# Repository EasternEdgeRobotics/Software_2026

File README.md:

# Software_2026

[Eastern Edge Robotics](https://www.easternedgerobotics.com/) (EER) is a student-led engineering design team based at the Memorial University of Newfoundland and the Fisheries and Marine Institute. The team competes in the annual MATE ROV Competition. Every year at EER, we build a small remotely-operated vehicle (ROV). This repository is EER's 2026 software package.

This code repository contains code for maintaining EER's current ROV, BlueStar.

## Table of Contents

- [Repository Structure](#repository-structure) 
    - [ros_workspace](#ros_workspace) 
    - [Tools](#Tools) 
    - [Assets](#Assets) 
    - [science_officer](#science_officer)

## Repository Structure

### ros_workspace
This project uses ROS2 Jazzy.

#### ROS2 Packages
| Package Name                                                            | Description                                                                                |
|-------------------------------------------------------------------------|--------------------------------------------------------------------------------------------|
| [**bluestar_backend**](./ros_workspace/src/bluestar_backend/)           | Backend code for interfacing with the ROV named BlueStar.                                  |
| [**bluestar_frotnend**](./ros_workspace/src/bluestar_frontend/)         | A C++ GUI for BlueStar made with ImGui, meant for driving the ROV named BlueStar.          |
| [**common_backend**](./ros_workspace/src/common_backend/)               | Common backend ROS nodes for all ROVs.                                                     |
| [**eer_interfaces**](./ros_workspace/src/eer_interfaces/)               | Custom ROS2 interfaces used by all packages.                                               |

More details [here](./ros_workspace/)

### Tools
Assorted tools useful for BlueStar, or developing for BlueStar.

### Assets
Assets used in BlueStar.

### science_officer
Tools related to the science officer tasks in the MATE 2026 mission.

### Firmware
The firmware running on BlueStar's onboard RP2040 microcontroller, which communicates with the onboard Raspberry Pi 4B via I2c, along with the PCB schematics can be found in the [Electrical_2026 Repository](https://github.com/EasternEdgeRobotics/Electrical_2026).

### Agentic AI Tools
Agentic AI tools, such as the Github Copilot Extension, should automatically use the [copilot-instructions.md](./.github/copilot-instructions.md) file for context. This file contains useful technical information for onboarding in natural language.

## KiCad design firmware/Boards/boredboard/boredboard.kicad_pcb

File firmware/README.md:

# Firmware

## LapisLazuli

The [LapisLazuli](./LapisLazuli/) folder contains the firmware for the RP2040 onboard Bluestar's tooling board (called LapisLazuli). It includes code for interfacing with the topides code (see [ros_workpace](../ros_workspace/README.md)) via UART and controlling Bluestar's peripherals.

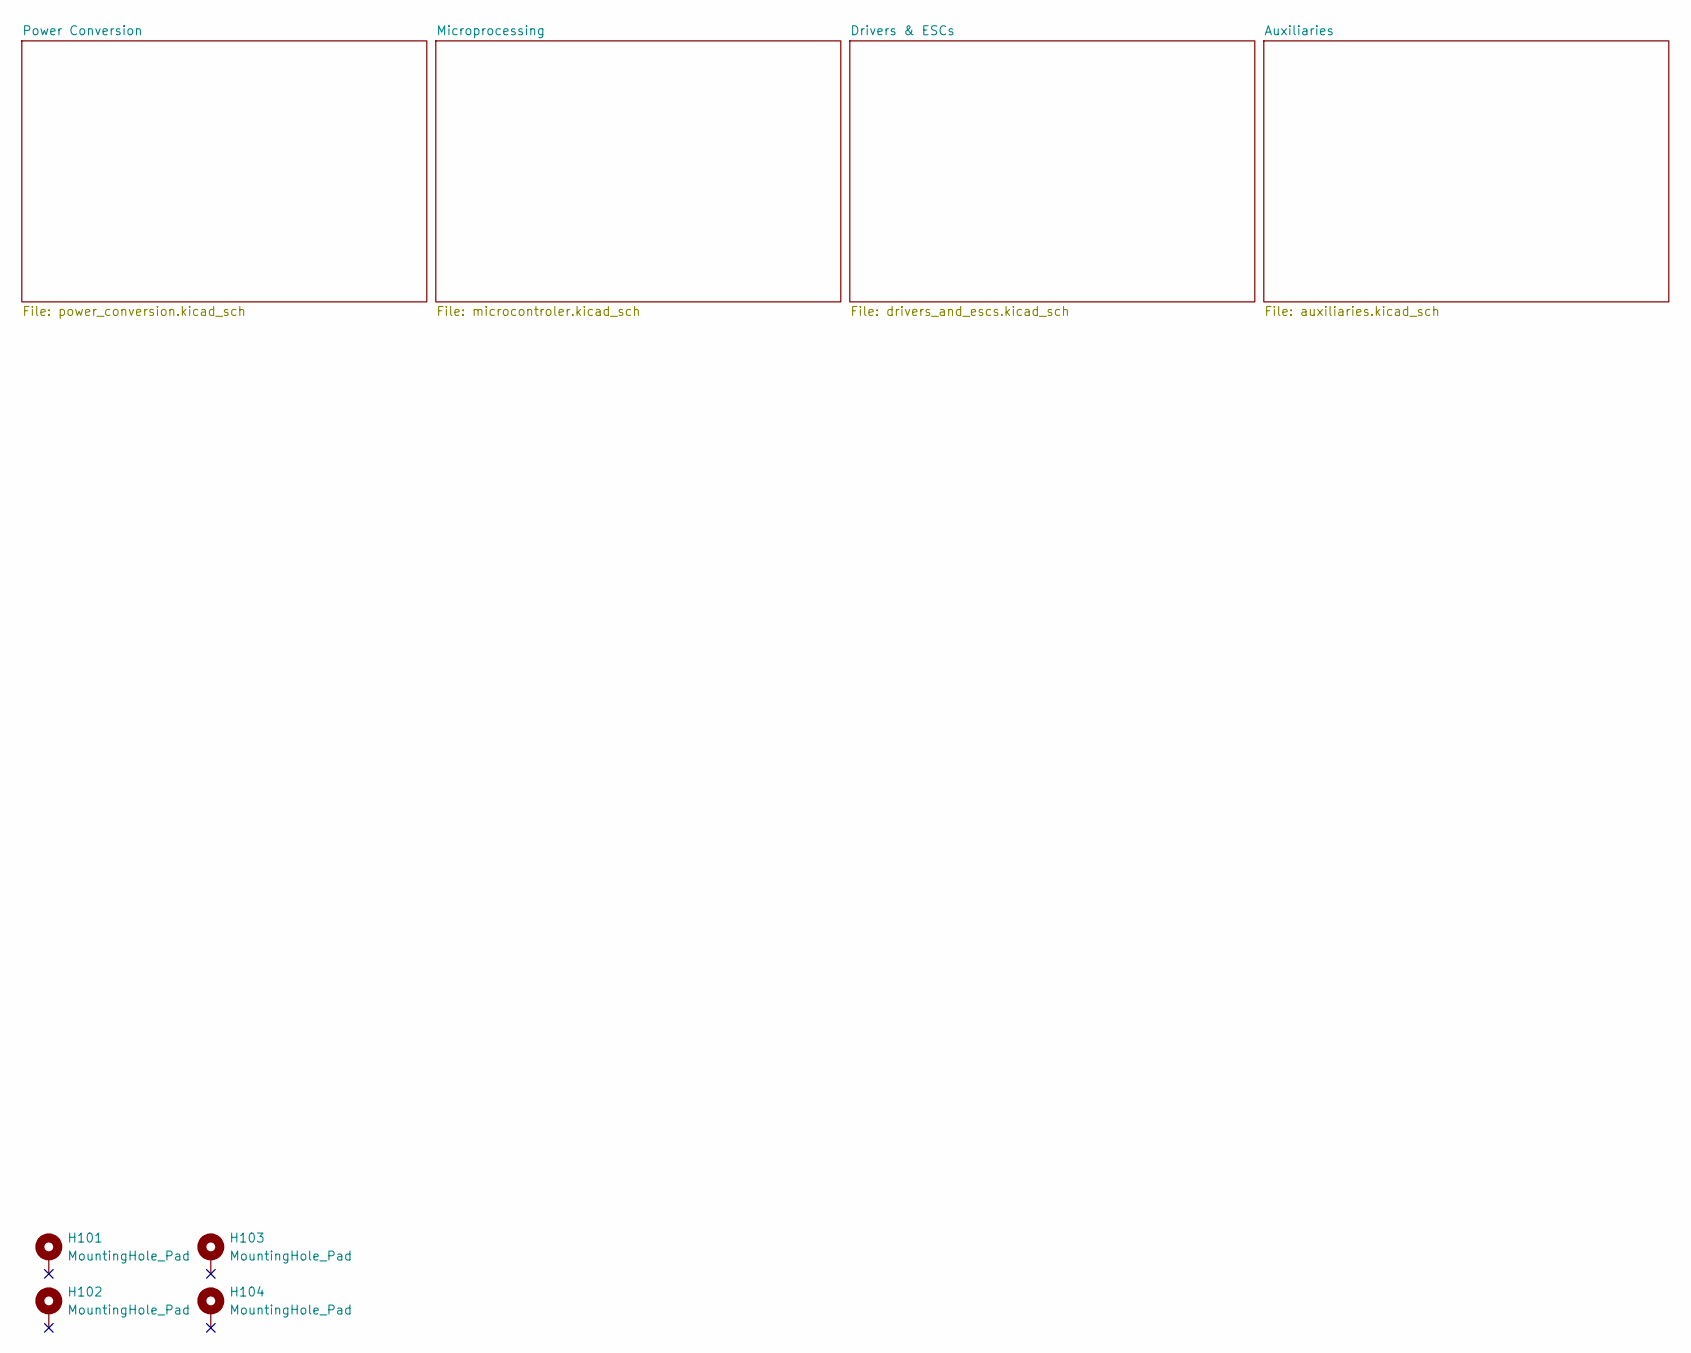
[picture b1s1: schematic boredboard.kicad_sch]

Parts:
H101, H102, H103, H104: MountingHole_Pad; MountingHole_2.7mm_M2.5_Pad

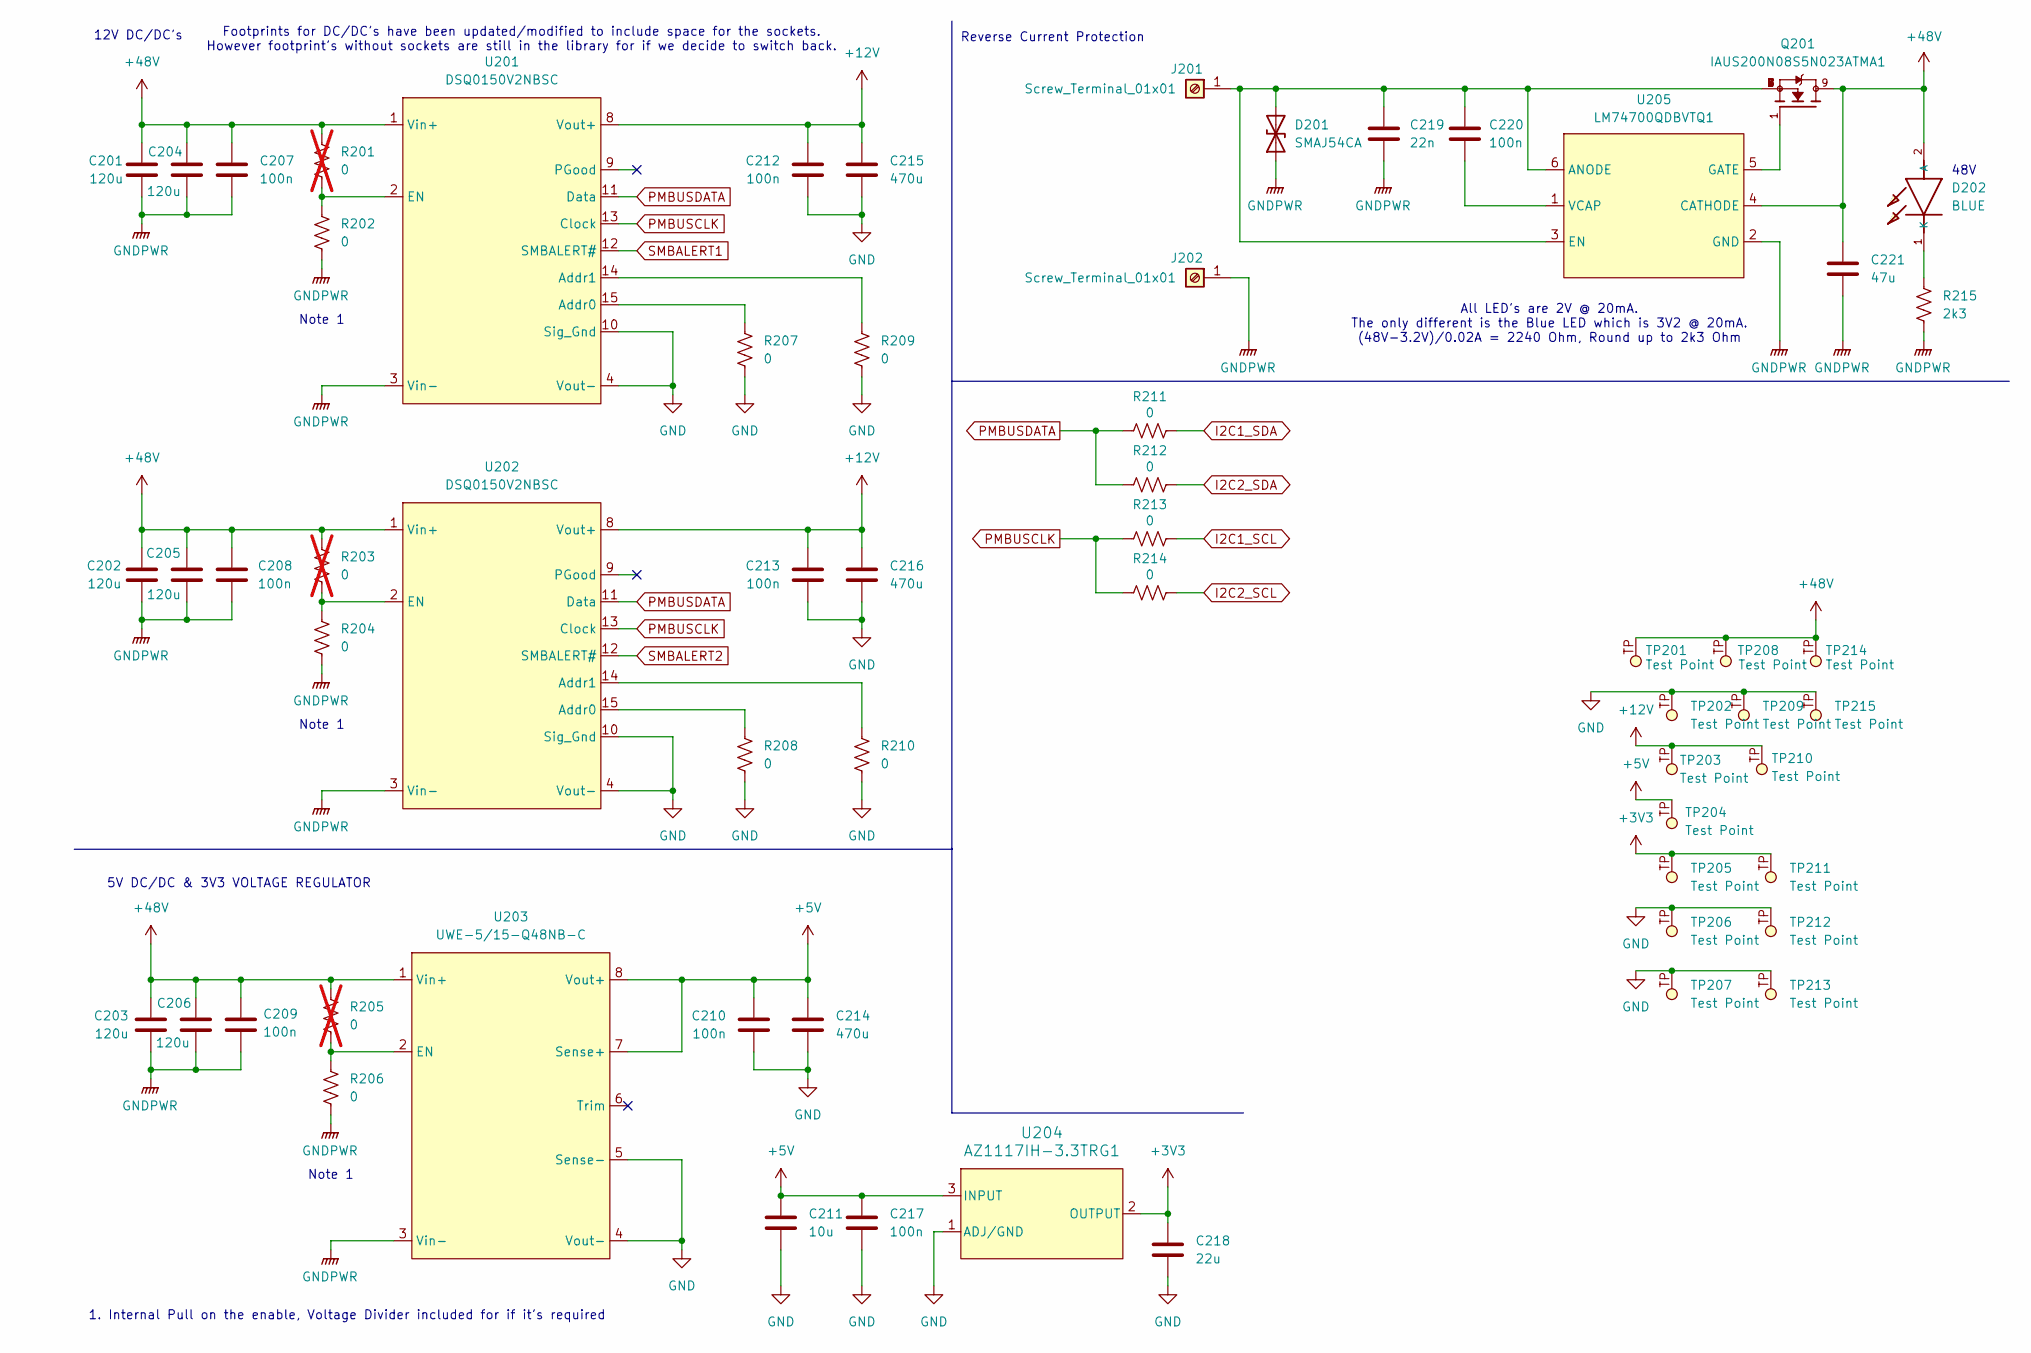
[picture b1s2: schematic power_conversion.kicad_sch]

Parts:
C201, C202, C203, C204, C205, C206: 120u; CP_Elec_10x12.6; DigiKey PN 399-A785MS127M1JLAS028CT-ND
C207, C208, C209, C210, C212, C213, C217, C220: 100n; C_0603_1608Metric; DigiKey PN 311-1344-1-ND
C211: 10u; CAP_CC1210_YAG; DigiKey PN 311-2035-1-ND
C214, C215, C216: 470u; CP_Elec_10x12.6; DigiKey PN 399-A768MS477M1ELAS017CT-ND
C218: 22u; CP_Elec_4x5.7; DigiKey PN 311-1860-1-ND
C219: 22n; C_0603_1608Metric; DigiKey PN 311-1138-1-ND
C221: 47u; C_0603_1608Metric; DigiKey PN 565-KTJ500B476M76BFT00CT-ND
D201: SMAJ54CA; DIOM4325X250N; DigiKey PN SMAJ54CALFCT-ND
D202: BLUE; LED_0603_1608Metric; DigiKey PN 732-4966-1-ND
J201, J202: Screw_Terminal_01x01; Ring_Terminal; DigiKey PN 36-7771-ND
Q201: IAUS200N08S5N023ATMA1; DigiKey PN IAUS200N08S5N023ATMA1CT-ND
R201, R203, R205: 0; R_0603_1608Metric; DigiKey PN 311-0.0GRCT-ND; not fitted
R202, R204, R206, R207, R208, R209, R210, R211, R212, R213, R214: 0; R_0603_1608Metric; DigiKey PN 311-0.0GRCT-ND
R215: 2k3; R_0603_1608Metric; DigiKey PN 13-RT0603BRE075KLCT-ND
TP201, TP202, TP203, TP204, TP205, TP206, TP207, TP208, TP209, TP210, TP211, TP212, TP213, TP214, TP215: Test Point; KEYSTONE_5019; DigiKey PN 36-5019TCT-ND
U201, U202: DSQ0150V2NBSC; DigiKey PN DSQ0150V2NBSC-ND
U203: UWE-5/15-Q48NB-C; CONV_UWE-24_3-Q12P-C; DigiKey PN 811-2240-5-ND
U204: AZ1117IH-3.3TRG1; SOT-223-3_TabPin2; DigiKey PN AZ1117IH-3.3TRG1DITR-ND
U205: LM74700QDBVTQ1; DBV0006A_N; DigiKey PN 296-53420-1-ND

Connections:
+3V3: C218.1, TP205.TP, TP211.TP, U204.2 (OUTPUT); also elsewhere on the board
+5V: C210.1, C211.1, C214.1, C217.1, TP204.TP, U203.7 (Sense+), U203.8 (Vout+), U204.3 (INPUT); also elsewhere on the board
+12V: C212.1, C213.1, C215.1, C216.1, TP203.TP, TP210.TP, U201.8 (Vout+), U202.8 (Vout+); also elsewhere on the board
+48V: C201.1, C202.1, C203.1, C204.1, C205.1, C206.1, C207.1, C208.1, C209.1, C221.1, D202.2 (A), Q201.9, R201.1, R203.1, R205.1, TP201.TP, TP208.TP, TP214.TP, U201.1 (Vin+), U202.1 (Vin+), U203.1 (Vin+), U205.4 (CATHODE)
GND: C210.2, C211.2, C212.2, C213.2, C214.2, C215.2, C216.2, C217.2, C218.2, R207.1, R208.1, R209.1, R210.1, TP202.TP, TP206.TP, TP207.TP, TP209.TP, TP212.TP, TP213.TP, TP215.TP, U201.4 (Vout-), U201.10 (Sig_Gnd), U202.4 (Vout-), U202.10 (Sig_Gnd), U203.4 (Vout-), U203.5 (Sense-), U204.1 (ADJ/GND); also elsewhere on the board
GNDPWR: C201.2, C202.2, C203.2, C204.2, C205.2, C206.2, C207.2, C208.2, C209.2, C219.2, C221.2, D201.1 (A1), J202.1, R202.2, R204.2, R206.2, R215.2, U201.3 (Vin-), U202.3 (Vin-), U203.3 (Vin-), U205.2 (GND)
I2C1_SCL: R213.2; also elsewhere on the board
I2C1_SDA: R211.2; also elsewhere on the board
I2C2_SCL: R214.2; also elsewhere on the board
I2C2_SDA: R212.2; also elsewhere on the board
unnamed: C219.1, C220.1, D201.2 (A2), J201.1, Q201.2, Q201.3, Q201.4, Q201.5, Q201.6, Q201.7, Q201.8, U205.3 (EN), U205.6 (ANODE)
unnamed: D202.1 (K), R215.1
unnamed: R207.2, U201.15 (Addr0)
unnamed: R209.2, U201.14 (Addr1)
unnamed: R201.2, R202.1, U201.2 (EN)
unnamed: R208.2, U202.15 (Addr0)
unnamed: R210.2, U202.14 (Addr1)
unnamed: R203.2, R204.1, U202.2 (EN)
unnamed: R205.2, R206.1, U203.2 (EN)
unnamed: Q201.1, U205.5 (GATE)
unnamed: C220.2, U205.1 (VCAP)
PMBUSCLK: R213.1, R214.1, U201.13 (Clock), U202.13 (Clock)
PMBUSDATA: R211.1, R212.1, U201.11 (Data), U202.11 (Data)
SMBALERT1: U201.12 (SMBALERT#); also elsewhere on the board
SMBALERT2: U202.12 (SMBALERT#); also elsewhere on the board

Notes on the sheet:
Note 1
Reverse Current Protection
5V DC/DC & 3V3 VOLTAGE REGULATOR
12V DC/DC's
Footprints for DC/DC's have been updated/modified to include space for the sockets. However footprint's without sockets are still in the library for if we decide to switch back.
1. Internal Pull on the enable, Voltage Divider included for if it's required
All LED's are 2V @ 20mA. The only different is the Blue LED which is 3V2 @ 20mA. (48V-3.2V)/0.02A = 2240 Ohm, Round up to 2k3 Ohm
48V

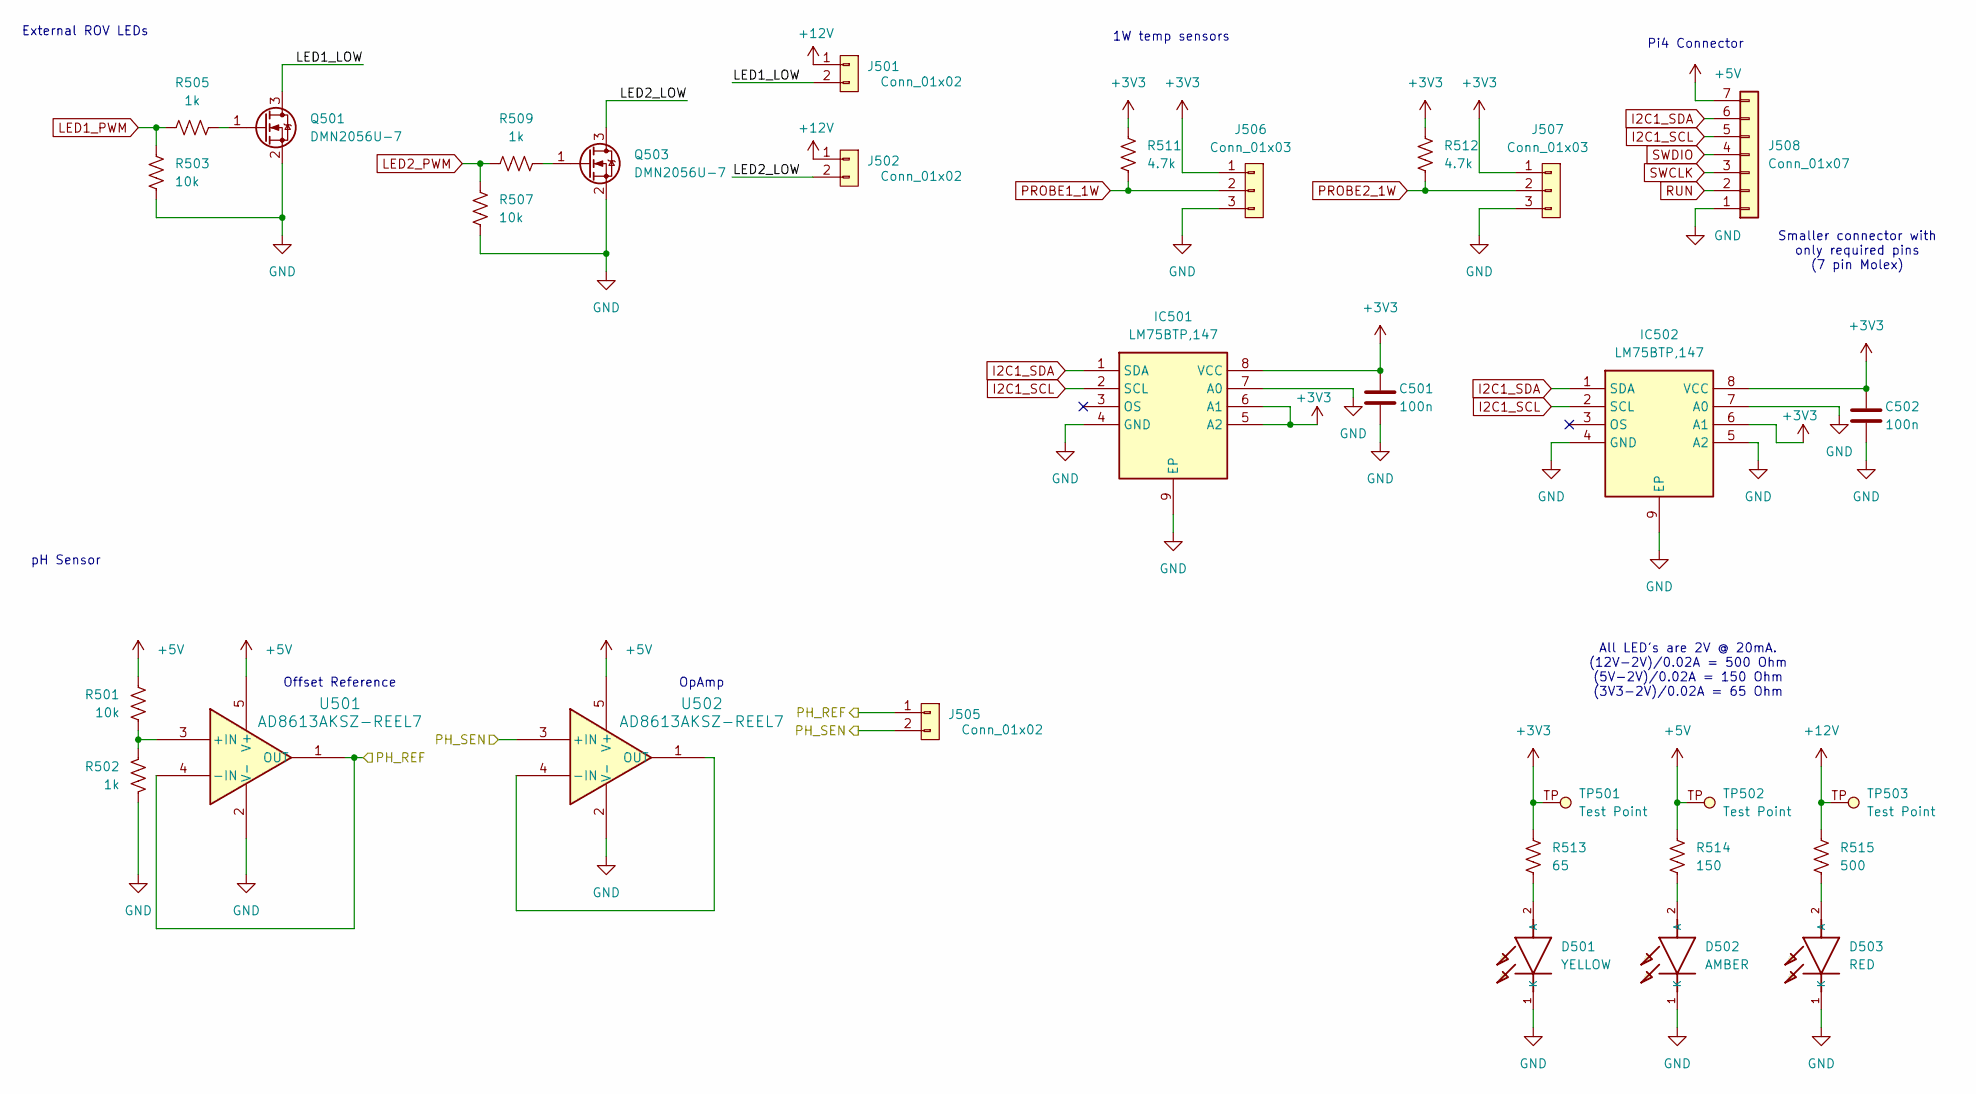
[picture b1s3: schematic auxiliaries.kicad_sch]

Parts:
C501, C502: 100n; C_0603_1608Metric; DigiKey PN 311-1344-1-ND
D501: YELLOW; LED_0603_1608Metric; DigiKey PN 732-4981-1-ND
D502: AMBER; LED_0603_1608Metric; DigiKey PN 732-150060AS75000CT-ND
D503: RED; LED_0603_1608Metric; DigiKey PN 732-4978-1-ND
IC501, IC502: LM75BTP,147; SON50P300X200X80-9N; Mouser Part Number 771-LM75BTP147
J501, J502, J505: Conn_01x02; Molex-43650-0227_-MFG; DigiKey PN WM4800-ND
J506, J507: Conn_01x03; MOLEX_436500327; DigiKey PN WM7500-ND
J508: Conn_01x07; MOLEX_436500727; DigiKey PN WM4805-ND
Q501, Q503: DMN2056U-7; SOT-23; DigiKey PN DMN2056U-7DICT-ND
R501, R503, R507: 10k; R_0603_1608Metric; DigiKey PN 311-10KGRCT-ND
R502, R505, R509: 1k; R_0603_1608Metric; DigiKey PN 311-1.00KHRCT-ND
R511, R512: 4.7k; R_0603_1608Metric; DigiKey PN 311-4.7KGRCT-ND
R513: 65; R_0603_1608Metric; DigiKey PN 311-1.00KHRCT-ND
R514: 150; R_0603_1608Metric; DigiKey PN 311-1.00KHRCT-ND
R515: 500; R_0603_1608Metric; DigiKey PN 311-1.00KHRCT-ND
TP501, TP502, TP503: Test Point; KEYSTONE_5019; DigiKey PN 36-5019TCT-ND
U501, U502: AD8613AKSZ-REEL7; KS_5_ADI; DigiKey PN 505-AD8613AKSZ-REEL7CT-ND

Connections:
+3V3: C501.2, C502.2, IC501.5 (A2), IC501.6 (A1), IC501.8 (VCC), IC502.6 (A1), IC502.8 (VCC), J506.1, J507.1, R511.1, R512.1, R513.1, TP501.TP; also elsewhere on the board
+5V: J508.7, R501.1, R514.1, TP502.TP, U501.5 (V+), U502.5 (V+); also elsewhere on the board
+12V: J501.1, J502.1, R515.1, TP503.TP; also elsewhere on the board
/Auxiliaries/LED1_LOW: J501.2, Q501.3 (D)
/Auxiliaries/LED2_LOW: J502.2, Q503.3 (D)
/Auxiliaries/PH_REF: J505.1, U501.1 (OUT), U501.4 (-IN)
/Auxiliaries/PH_SEN: J505.2, U502.3 (+IN)
GND: C501.1, C502.1, D501.1 (K), D502.1 (K), D503.1 (K), IC501.4 (GND), IC501.7 (A0), IC501.9 (EP), IC502.4 (GND), IC502.5 (A2), IC502.7 (A0), IC502.9 (EP), J506.3, J507.3, J508.1, Q501.2 (S), Q503.2 (S), R502.2, R503.2, R507.2, U501.2 (V-), U502.2 (V-); also elsewhere on the board
I2C1_SCL: IC501.2 (SCL), IC502.2 (SCL), J508.5; also elsewhere on the board
I2C1_SDA: IC501.1 (SDA), IC502.1 (SDA), J508.6; also elsewhere on the board
LED1_PWM: R503.1, R505.1; also elsewhere on the board
LED2_PWM: R507.1, R509.1; also elsewhere on the board
unnamed: D501.2 (A), R513.2
unnamed: D502.2 (A), R514.2
unnamed: D503.2 (A), R515.2
unnamed: Q501.1 (G), R505.2
unnamed: Q503.1 (G), R509.2
unnamed: R501.2, R502.1, U501.3 (+IN)
unnamed: U502.1 (OUT), U502.4 (-IN)
PROBE1_1W: J506.2, R511.2; also elsewhere on the board
PROBE2_1W: J507.2, R512.2; also elsewhere on the board
RUN: J508.2; also elsewhere on the board
SWCLK: J508.3; also elsewhere on the board
SWDIO: J508.4; also elsewhere on the board

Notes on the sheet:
External ROV LEDs
All LED's are 2V @ 20mA. (12V-2V)/0.02A = 500 Ohm (5V-2V)/0.02A = 150 Ohm (3V3-2V)/0.02A = 65 Ohm
OpAmp
Smaller connector with only required pins (7 pin Molex)
Offset Reference
1W temp sensors
Pi4 Connector
pH Sensor

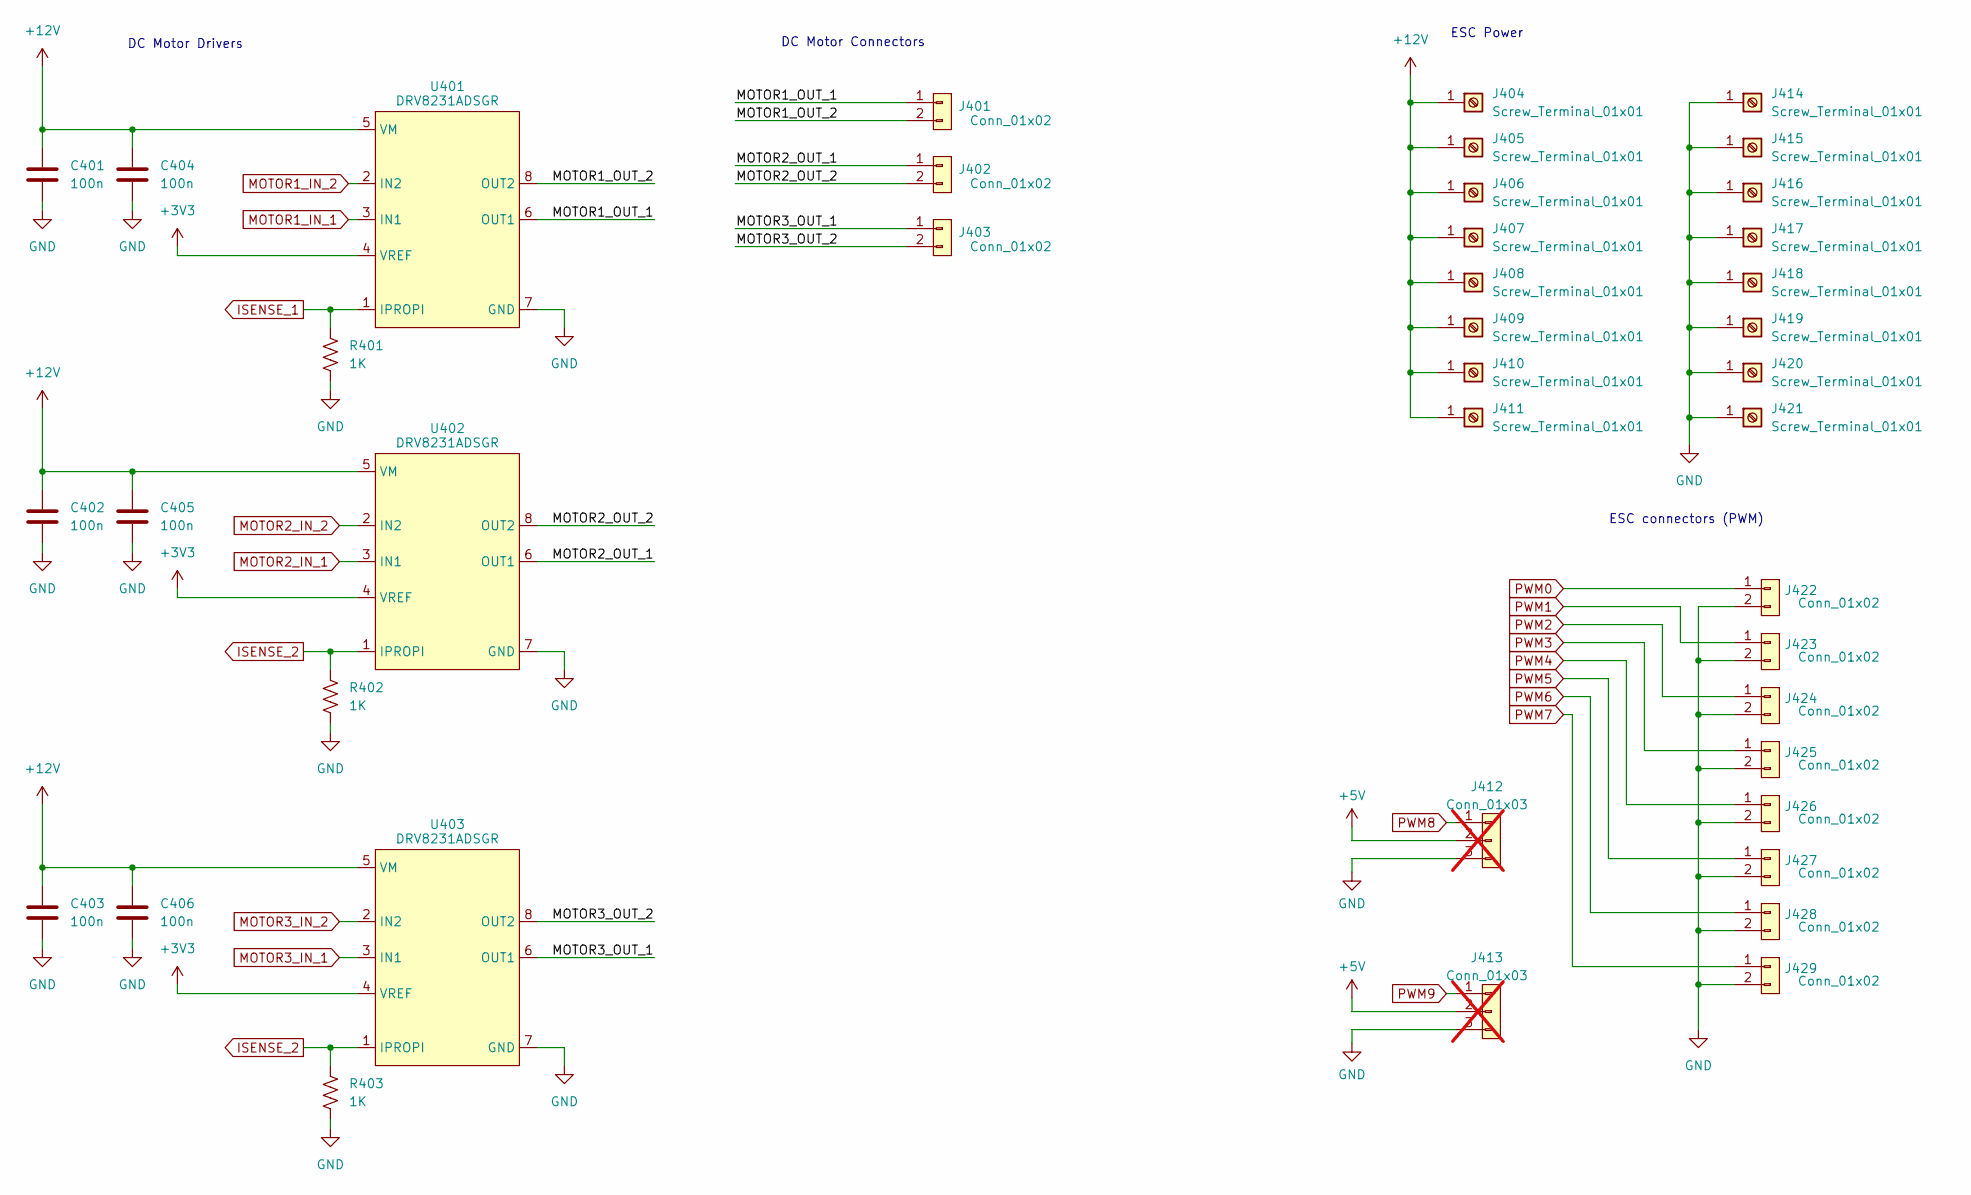
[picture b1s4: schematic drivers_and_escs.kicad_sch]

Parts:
C401, C402, C403, C404, C405, C406: 100n; C_0603_1608Metric; DigiKey PN 311-1344-1-ND
J401, J402, J403, J422, J423, J424, J425, J426, J427, J428, J429: Conn_01x02; Molex-43650-0227_-MFG; DigiKey PN WM4800-ND
J404, J405, J406, J407, J408, J409, J410, J411, J414, J415, J416, J417, J418, J419, J420, J421: Screw_Terminal_01x01; Ring_Terminal; DigiKey PN 36-7771-ND
J412, J413: Conn_01x03; MOLEX_436500327; DigiKey PN WM7500-ND; not fitted
R401, R402, R403: 1K; R_0603_1608Metric; DigiKey PN 311-1.00KHRCT-ND
U401, U402, U403: DRV8231ADSGR; WSON8_DSG_TEX; DigiKey PN 296-DRV8231ADSGRCT-ND

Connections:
+3V3: U401.4 (VREF), U402.4 (VREF), U403.4 (VREF); also elsewhere on the board
+12V: C401.1, C402.1, C403.1, C404.1, C405.1, C406.1, J404.1, J405.1, J406.1, J407.1, J408.1, J409.1, J410.1, J411.1, U401.5 (VM), U402.5 (VM), U403.5 (VM); also elsewhere on the board
/Drivers & ESCs/MOTOR1_OUT_1: J401.1, U401.6 (OUT1)
/Drivers & ESCs/MOTOR1_OUT_2: J401.2, U401.8 (OUT2)
/Drivers & ESCs/MOTOR2_OUT_1: J402.1, U402.6 (OUT1)
/Drivers & ESCs/MOTOR2_OUT_2: J402.2, U402.8 (OUT2)
/Drivers & ESCs/MOTOR3_OUT_1: J403.1, U403.6 (OUT1)
/Drivers & ESCs/MOTOR3_OUT_2: J403.2, U403.8 (OUT2)
GND: C401.2, C402.2, C403.2, C404.2, C405.2, C406.2, J412.3, J413.3, J414.1, J415.1, J416.1, J417.1, J418.1, J419.1, J420.1, J421.1, J422.2, J423.2, J424.2, J425.2, J426.2, J427.2, J428.2, J429.2, R401.2, R402.2, R403.2, U401.7 (GND), U402.7 (GND), U403.7 (GND); also elsewhere on the board
ISENSE_1: R401.1, U401.1 (IPROPI)
ISENSE_2: R402.1, R403.1, U402.1 (IPROPI), U403.1 (IPROPI)
MOTOR1_IN_1: U401.3 (IN1); also elsewhere on the board
MOTOR1_IN_2: U401.2 (IN2); also elsewhere on the board
MOTOR2_IN_1: U402.3 (IN1); also elsewhere on the board
MOTOR2_IN_2: U402.2 (IN2); also elsewhere on the board
MOTOR3_IN_1: U403.3 (IN1); also elsewhere on the board
MOTOR3_IN_2: U403.2 (IN2); also elsewhere on the board
unnamed: J412.2, J413.2
PWM0: J422.1; also elsewhere on the board
PWM1: J423.1; also elsewhere on the board
PWM2: J424.1; also elsewhere on the board
PWM3: J425.1; also elsewhere on the board
PWM4: J426.1; also elsewhere on the board
PWM5: J427.1; also elsewhere on the board
PWM6: J428.1; also elsewhere on the board
PWM7: J429.1; also elsewhere on the board

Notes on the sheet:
ESC connectors (PWM)
DC Motor Connectors
DC Motor Drivers
ESC Power

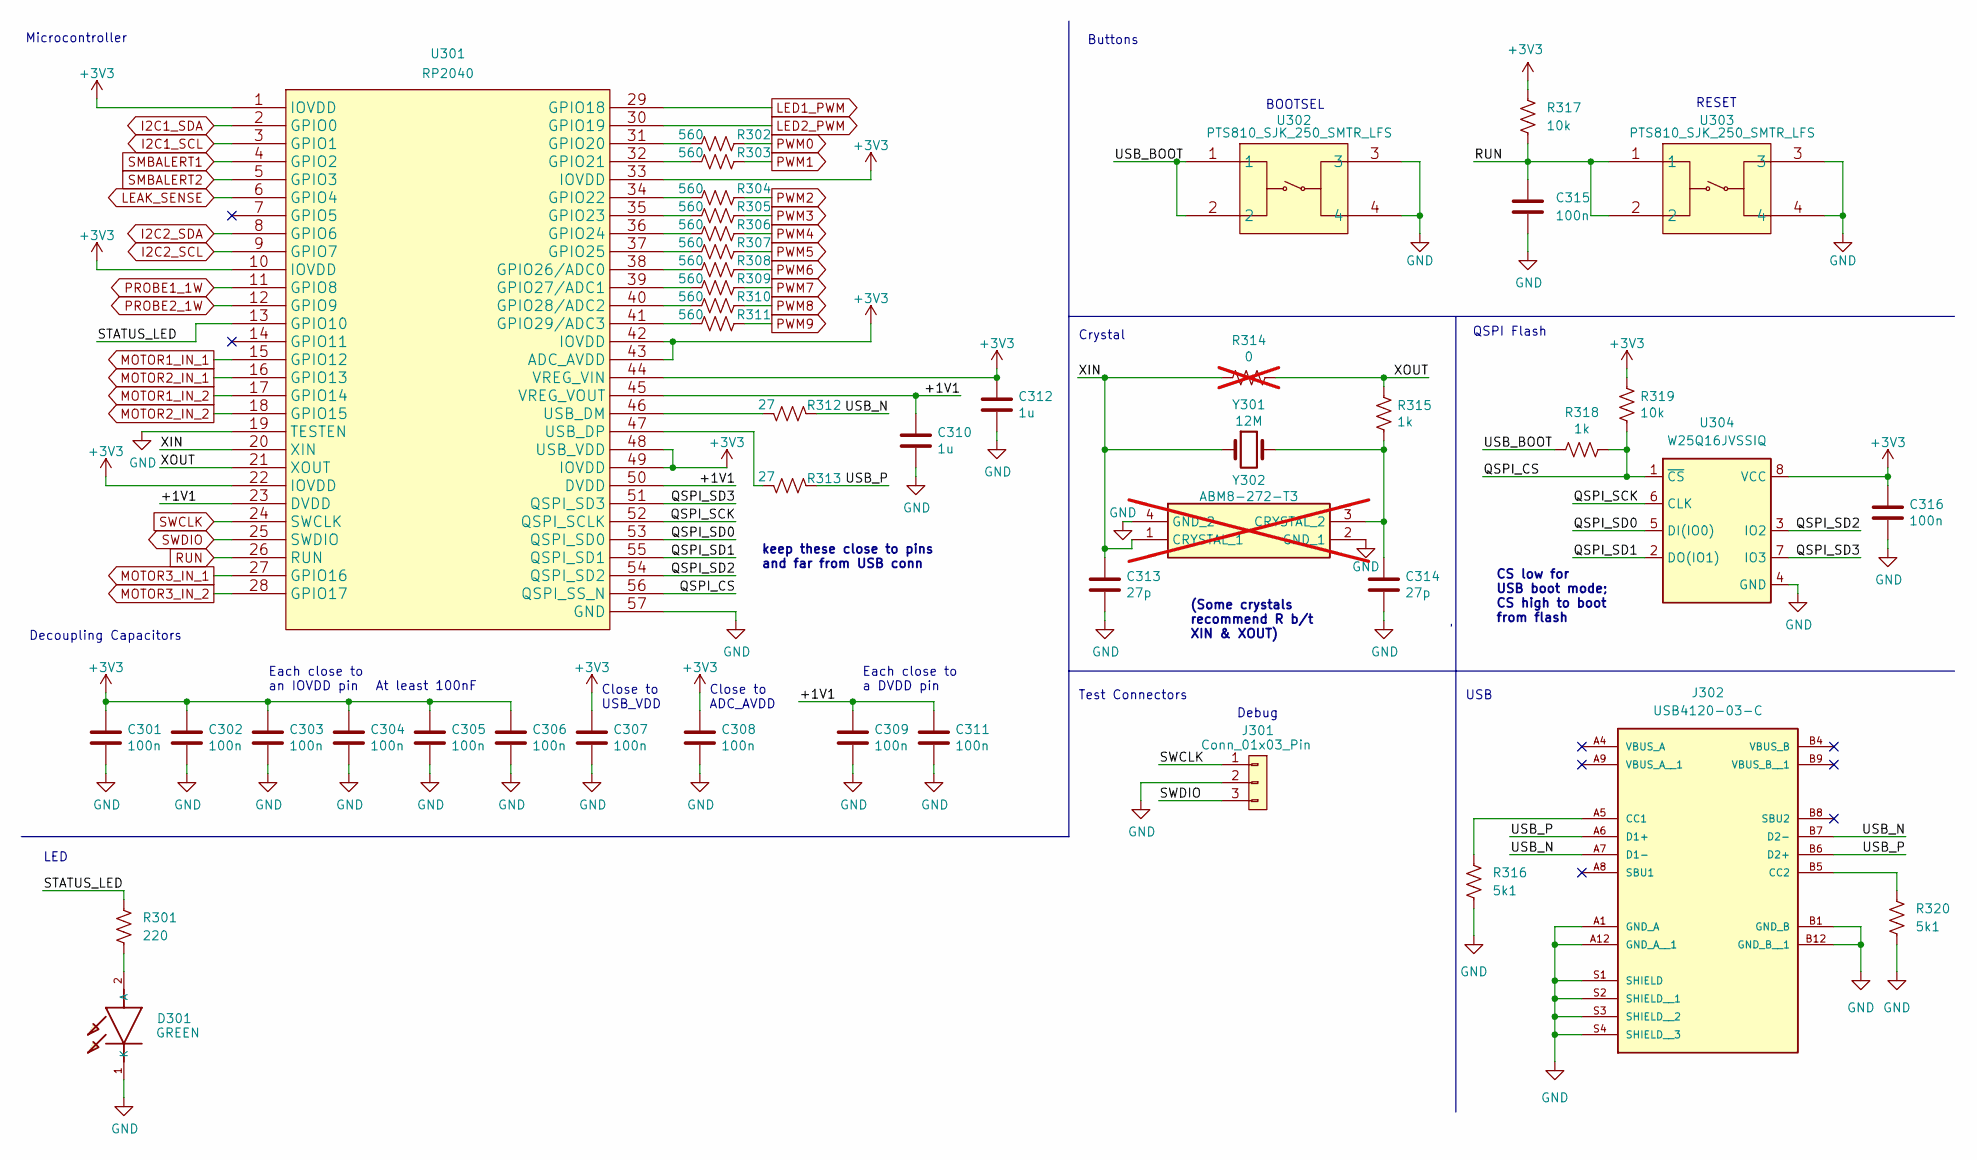
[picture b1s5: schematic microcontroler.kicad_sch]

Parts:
C301, C302, C303, C304, C305, C306, C307, C308, C309, C311, C315, C316: 100n; C_0603_1608Metric; DigiKey PN 311-1344-1-ND
C310, C312: 1u; C_0603_1608Metric; DigiKey PN 1276-6524-1-ND
C313, C314: 27p; C_0603_1608Metric; DigiKey PN 311-1063-1-ND
D301: GREEN; LED_0603_1608Metric; MOUSER_PART_NUMBER 710-150060VS75000
J301: Conn_01x03_Pin; PinHeader_1x03_P2.54mm_Vertical; DigiKey PN WM4301-ND
J302: USB4120-03-C; GCT_USB4120-03-C_REVA; PARTREV A; DigiKey PN 2073-USB4120-03-CCT-ND
R301: 220; R_0603_1608Metric; DigiKey PN 311-220HRCT-ND
R302, R303, R304, R305, R306, R307, R308, R309, R310, R311: 560; R_0603_1608Metric; DigiKey PN 311-0.0GRCT-ND
R312, R313: 27; R_0603_1608Metric; DigiKey PN 311-27.0HRCT-ND
R314: 0; R_0603_1608Metric; DigiKey PN 311-0.0GRCT-ND; not fitted
R315, R318: 1k; R_0603_1608Metric; DigiKey PN 311-1.00KHRCT-ND
R316, R320: 5k1; R_0603_1608Metric; DigiKey PN 311-5.10KHRCT-ND
R317, R319: 10k; R_0603_1608Metric; DigiKey PN 311-10KGRCT-ND
U301: RP2040; QFN-56-1EP_7x7mm_P0.4mm_EP3.2x3.2mm; DigiKey PN 2648-SC0914(13)CT-ND
U302, U303: PTS810_SJK_250_SMTR_LFS; PTS810SJG250SMTRLFS; DigiKey PN CKN10503CT-ND
U304: W25Q16JVSSIQ; SOIC-8_5.23x5.23mm_P1.27mm; DigiKey PN W25Q16JVSSIQ-ND
Y301: 12M; XTAL_ABLS7M-12.000MHZ-B-2-T; DigiKey PN 535-13415-1-ND
Y302: ABM8-272-T3; ABM8272T3; Mouser Part Number 815-ABM8-272-T3; not fitted

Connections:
+3V3: C301.1, C302.1, C303.1, C304.1, C305.1, C306.1, C307.1, C308.1, C312.1, C316.1, R317.1, R319.1, U301.1 (IOVDD), U301.10 (IOVDD), U301.22 (IOVDD), U301.33 (IOVDD), U301.42 (IOVDD), U301.43 (ADC_AVDD), U301.44 (VREG_VIN), U301.48 (USB_VDD), U301.49 (IOVDD), U304.8 (VCC); also elsewhere on the board
/Microprocessing/+1V1: C309.1, C310.1, C311.1, U301.23 (DVDD), U301.45 (VREG_VOUT), U301.50 (DVDD)
/Microprocessing/QSPI_CS: R318.1, R319.2, U301.56 (QSPI_SS_N), U304.1 (~CS)
/Microprocessing/QSPI_SCK: U301.52 (QSPI_SCLK), U304.6 (CLK)
/Microprocessing/QSPI_SD0: U301.53 (QSPI_SD0), U304.5 (DI(IO0))
/Microprocessing/QSPI_SD1: U301.55 (QSPI_SD1), U304.2 (DO(IO1))
/Microprocessing/QSPI_SD2: U301.54 (QSPI_SD2), U304.3 (IO2)
/Microprocessing/QSPI_SD3: U301.51 (QSPI_SD3), U304.7 (IO3)
/Microprocessing/STATUS_LED: R301.1, U301.13 (GPIO10)
/Microprocessing/USB_BOOT: R318.2, U302.1, U302.2
/Microprocessing/USB_N: J302.A7 (D1-), J302.B7 (D2-), R312.1
/Microprocessing/USB_P: J302.A6 (D1+), J302.B6 (D2+), R313.1
/Microprocessing/XIN: C313.1, R314.2, U301.20 (XIN), Y301.1, Y302.1 (CRYSTAL_1)
/Microprocessing/XOUT: R314.1, R315.1, U301.21 (XOUT)
GND: C301.2, C302.2, C303.2, C304.2, C305.2, C306.2, C307.2, C308.2, C309.2, C310.2, C311.2, C312.2, C313.2, C314.2, C315.2, C316.2, D301.1 (K), J301.2, J302.A1 (GND_A), J302.A12 (GND_A__1), J302.B1 (GND_B), J302.B12 (GND_B__1), J302.S1 (SHIELD), J302.S2 (SHIELD__1), J302.S3 (SHIELD__2), J302.S4 (SHIELD__3), R316.2, R320.2, U301.19 (TESTEN), U301.57 (GND), U302.3, U302.4, U303.3, U303.4, U304.4 (GND), Y302.2 (GND_1), Y302.4 (GND_2); also elsewhere on the board
I2C1_SCL: U301.3 (GPIO1); also elsewhere on the board
I2C1_SDA: U301.2 (GPIO0); also elsewhere on the board
I2C2_SCL: U301.9 (GPIO7); also elsewhere on the board
I2C2_SDA: U301.8 (GPIO6); also elsewhere on the board
LEAK_SENSE: U301.6 (GPIO4)
LED1_PWM: U301.29 (GPIO18); also elsewhere on the board
LED2_PWM: U301.30 (GPIO19); also elsewhere on the board
MOTOR1_IN_1: U301.15 (GPIO12); also elsewhere on the board
MOTOR1_IN_2: U301.17 (GPIO14); also elsewhere on the board
MOTOR2_IN_1: U301.16 (GPIO13); also elsewhere on the board
MOTOR2_IN_2: U301.18 (GPIO15); also elsewhere on the board
MOTOR3_IN_1: U301.27 (GPIO16); also elsewhere on the board
MOTOR3_IN_2: U301.28 (GPIO17); also elsewhere on the board
unnamed: D301.2 (A), R301.2
unnamed: J302.A5 (CC1), R316.1
unnamed: J302.B5 (CC2), R320.1
unnamed: R302.2, U301.31 (GPIO20)
unnamed: R303.2, U301.32 (GPIO21)
unnamed: R304.2, U301.34 (GPIO22)
unnamed: R305.2, U301.35 (GPIO23)
unnamed: R306.2, U301.36 (GPIO24)
unnamed: R307.2, U301.37 (GPIO25)
unnamed: R308.2, U301.38 (GPIO26/ADC0)
unnamed: R309.2, U301.39 (GPIO27/ADC1)
unnamed: R310.2, U301.40 (GPIO28/ADC2)
unnamed: R311.2, U301.41 (GPIO29/ADC3)
unnamed: R312.2, U301.46 (USB_DM)
unnamed: R313.2, U301.47 (USB_DP)
unnamed: C314.1, R315.2, Y301.2, Y302.3 (CRYSTAL_2)
PROBE1_1W: U301.11 (GPIO8); also elsewhere on the board
PROBE2_1W: U301.12 (GPIO9); also elsewhere on the board
PWM0: R302.1; also elsewhere on the board
PWM1: R303.1; also elsewhere on the board
PWM2: R304.1; also elsewhere on the board
PWM3: R305.1; also elsewhere on the board
PWM4: R306.1; also elsewhere on the board
PWM5: R307.1; also elsewhere on the board
PWM6: R308.1; also elsewhere on the board
PWM7: R309.1; also elsewhere on the board
PWM8: R310.1
PWM9: R311.1
RUN: C315.1, R317.2, U301.26 (RUN), U303.1, U303.2; also elsewhere on the board
SMBALERT1: U301.4 (GPIO2); also elsewhere on the board
SMBALERT2: U301.5 (GPIO3); also elsewhere on the board
SWCLK: J301.1, U301.24 (SWCLK); also elsewhere on the board
SWDIO: J301.3, U301.25 (SWDIO); also elsewhere on the board

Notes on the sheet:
At least 100nF
Microcontroller
Close to USB_VDD
keep these close to pins and far from USB conn
Decoupling Capacitors
Test Connectors
USB
Close to ADC_AVDD
Each close to a DVDD pin
BOOTSEL
CS low for USB boot mode; CS high to boot from flash
Debug
LED
QSPI Flash
RESET
Crystal
Buttons
Each close to an IOVDD pin
(Some crystals recommend R b/t XIN & XOUT)
